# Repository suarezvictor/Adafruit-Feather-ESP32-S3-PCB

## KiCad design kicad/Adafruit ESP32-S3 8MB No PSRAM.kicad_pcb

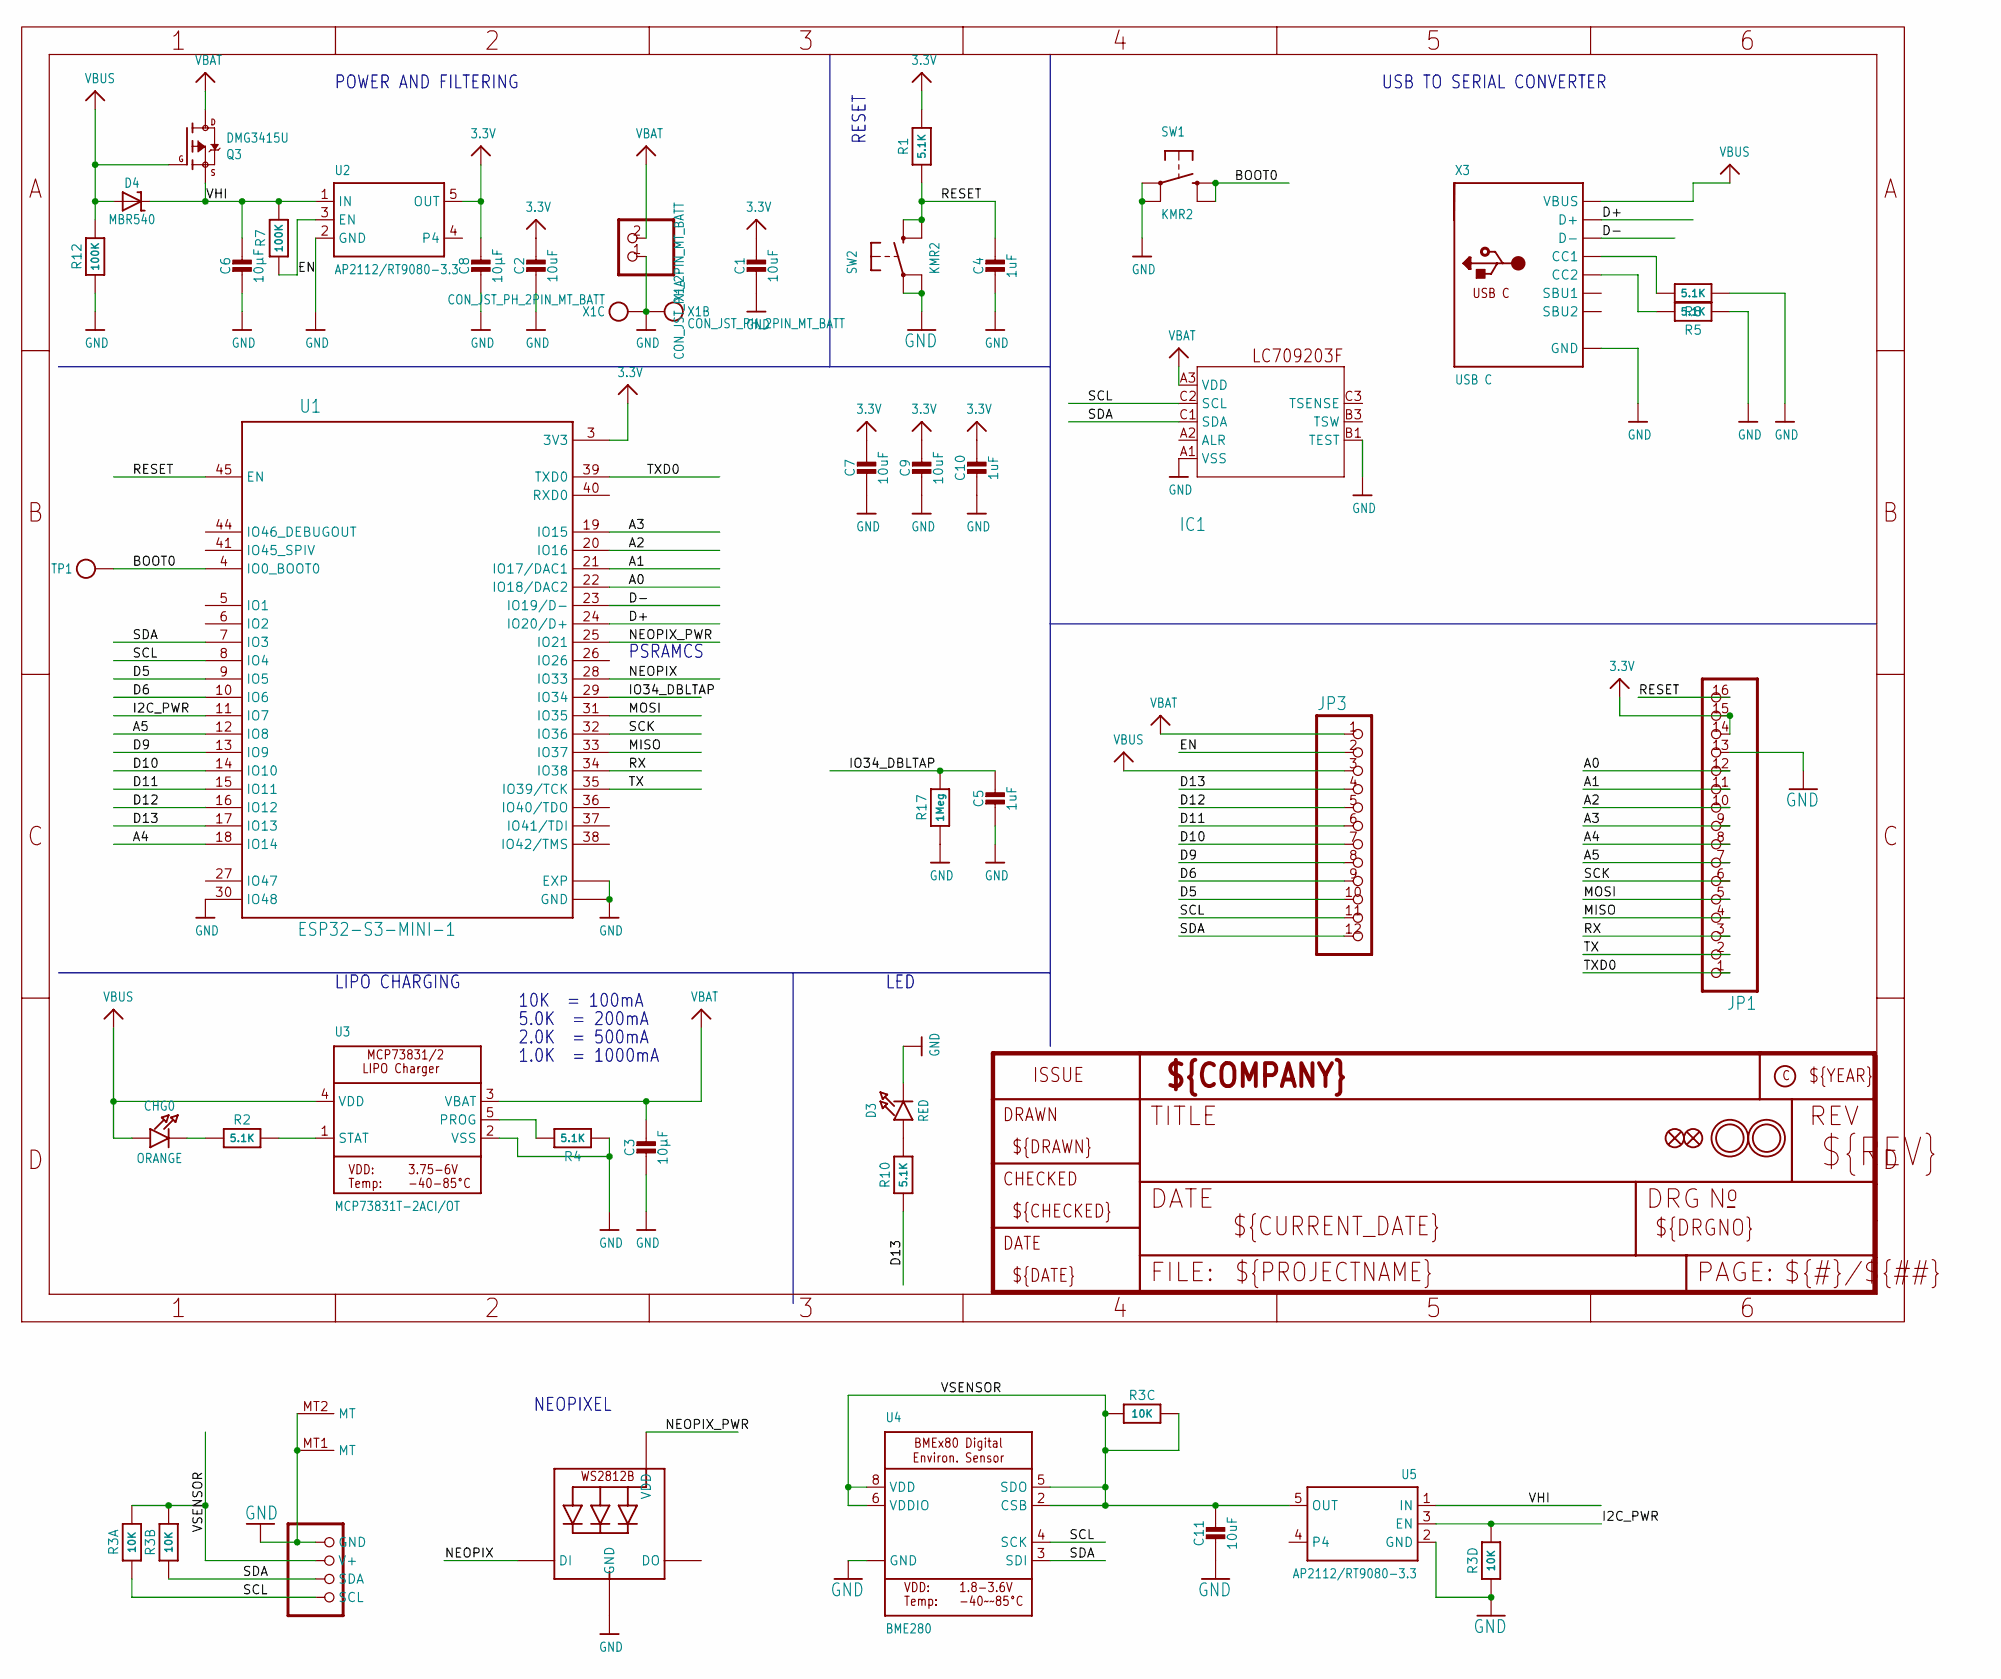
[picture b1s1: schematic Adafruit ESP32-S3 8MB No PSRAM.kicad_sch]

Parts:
C1, C2, C7, C9: 10uF; 0805-NO
C3, C6, C8: 10µF; 0805-NO
C4, C5, C10: 1uF; 0603-NO
C11: 10uF; _0805MP
CHG0: ORANGE; CHIPLED_0603_NOOUTLINE
CONN1: STEMMA_I2C_QTRA; JST_SH4_RA
D3: RED; CHIPLED_0603_NOOUTLINE
D4: MBR540; SOD-123
IC1: LC709203F/MH; WLCSP9
JP1: HEADER-1X16ROUND; 1X16_ROUND
JP3: HEADER-1X12; 1X12_ROUND
LED1: WS2812B_SK6805_1515; SK6805_1515
Q3: DMG3415U; SOT23-R
R1, R2, R4, R5, R8, R10: 5.1K; 0603-NO
R3: 10K; RESPACK_4X0603
R7, R12: 100K; 0603-NO
R17: 1Meg; 0603-NO
SW1, SW2: KMR2; BTN_KMR2_4.6X2.8
TP1: TESTPOINTROUND1.5MMNO; TESTPOINT_ROUND_1.5MM_NO
U1: ESP32-S3-MINI-1; QFN60_ESP32-S2-MINI-1_EXP
U2, U5: AP2112/RT9080-3.3; SOT23-5
U3: MCP73831T-2ACI/OT; SOT23-5
U4: BME280
U$31, U$32: MOUNTINGHOLE2.5; MOUNTINGHOLE_2.5_PLATED
U$34, U$35: FIDUCIAL_1MM
X1: CON_JST_PH_2PIN_MT_BATT; JSTPH2_BATT
X3: USB C; USB_C_CUSB31-CFM2AX-01-X

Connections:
3.3V: C1.1, C2.1, C7.1, C8.1, C9.1, C10.1, JP1.14, JP1.15, R1.2, U1.3 (3V3), U2.5 (OUT)
A0: JP1.12, U1.22 (IO18/DAC2)
A1: JP1.11, U1.21 (IO17/DAC1)
A2: JP1.10, U1.20 (IO16)
A3: JP1.9, U1.19 (IO15)
A4: JP1.8, U1.18 (IO14)
A5: JP1.7, U1.12 (IO8)
BOOT0: SW1.B (S), SW1.B' (S1), TP1.P$1, U1.4 (IO0_BOOT0)
D5: JP3.10, U1.9 (IO5)
D6: JP3.9, U1.10 (IO6)
D9: JP3.8, U1.13 (IO9)
D10: JP3.7, U1.14 (IO10)
D11: JP3.6, U1.15 (IO11)
D12: JP3.5, U1.16 (IO12)
D13: JP3.4, R10.1, U1.17 (IO13)
D+: U1.24 (IO20/D+), X3.A6 (D+), X3.B6 (D+)
D-: U1.23 (IO19/D-), X3.A7 (D-), X3.B7 (D-)
EN: JP3.2, R7.1, U2.3 (EN)
GND: C1.2, C2.2, C3.2, C4.2, C5.2, C6.2, C7.2, C8.2, C9.2, C10.2, C11.2, CONN1.1 (GND), CONN1.MT1 (MT), CONN1.MT2 (MT), D3.C, IC1.A1 (VSS), IC1.B1 (TEST), JP1.13, LED1.4 (GND), R3.4 (1), R4.1, R5.1, R8.1, R12.1, R17.1, SW1.A, SW1.A' (P1), SW2.A, SW2.A' (P1), U1.1 (GND), U1.2 (GND), U1.30 (IO48), U1.42 (GND), U1.43 (GND), U1.46 (GND), U1.47 (GND), U1.48 (GND), U1.49 (GND), U1.50 (GND), U1.51 (GND), U1.52 (GND), U1.53 (GND), U1.54 (GND), U1.55 (GND), U1.56 (GND), U1.57 (GND), U1.58 (GND), U1.59 (GND), U1.60 (GND), U1.61 (EXP), U1.62 (GND), U1.63 (GND), U1.64 (GND), U1.65 (GND), U1.66 (EXP), U1.67 (EXP), U1.68 (EXP), U1.69 (EXP), U1.70 (EXP), U1.71 (EXP), U1.72 (EXP), U1.73 (EXP), U2.2 (GND), U3.2 (VSS), U4.1 (GND), U4.7 (GND), U5.2 (GND), X1.1, X1.NC1, X1.NC2, X3.A1B12 (GND), X3.B1A12 (GND)
I2C_PWR: R3.5 (2), U1.11 (IO7), U5.3 (EN)
IO34_DBLTAP: C5.1, R17.2, U1.29 (IO34)
MISO: JP1.4, U1.33 (IO37)
MOSI: JP1.5, U1.31 (IO35)
unnamed: CHG0.C, R2.1
unnamed: R2.2, U3.1 (STAT)
unnamed: R4.2, U3.5 (PROG)
unnamed: D3.A, R10.2
unnamed: R8.2, X3.A5 (CC1)
unnamed: R5.2, X3.B5 (CC2)
NEOPIX: LED1.1 (DI), U1.28 (IO33)
NEOPIX_PWR: LED1.2 (VDD), U1.25 (IO21)
RESET: C4.1, JP1.16, R1.1, SW2.B (S), SW2.B' (S1), U1.45 (EN)
RX: JP1.3, U1.34 (IO38)
SCK: JP1.6, U1.32 (IO36)
SCL: CONN1.4 (SCL), IC1.C2 (SCL), JP3.11, R3.1, U1.8 (IO4), U4.4 (SCK)
SDA: CONN1.3 (SDA), IC1.C1 (SDA), JP3.12, R3.2 (1), U1.7 (IO3), U4.3 (SDI)
TX: JP1.2, U1.35 (IO39/TCK)
TXD0: JP1.1, U1.39 (TXD0)
VBAT: C3.1, IC1.A3 (VDD), JP3.1, Q3.3 (D), U3.3 (VBAT), X1.2
VBUS: CHG0.A, D4.A, JP3.3, Q3.1 (G), R12.2, U3.4 (VDD), X3.A4B9 (VBUS), X3.B4A9 (VBUS)
VHI: C6.1, D4.C, Q3.2 (S), R7.2, U2.1 (IN), U5.1 (IN)
VSENSOR: C11.1, CONN1.2 (V+), R3.3 (1), R3.6 (2), R3.7 (2), R3.8 (2), U4.2 (CSB), U4.5 (SDO), U4.6 (VDDIO), U4.8 (VDD), U5.5 (OUT)

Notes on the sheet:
2.0K = 500mA
POWER AND FILTERING
5.0K = 200mA
RESET
USB TO SERIAL CONVERTER
LIPO CHARGING
PSRAMCS
1.0K = 1000mA
LED
NEOPIXEL
10K = 100mA

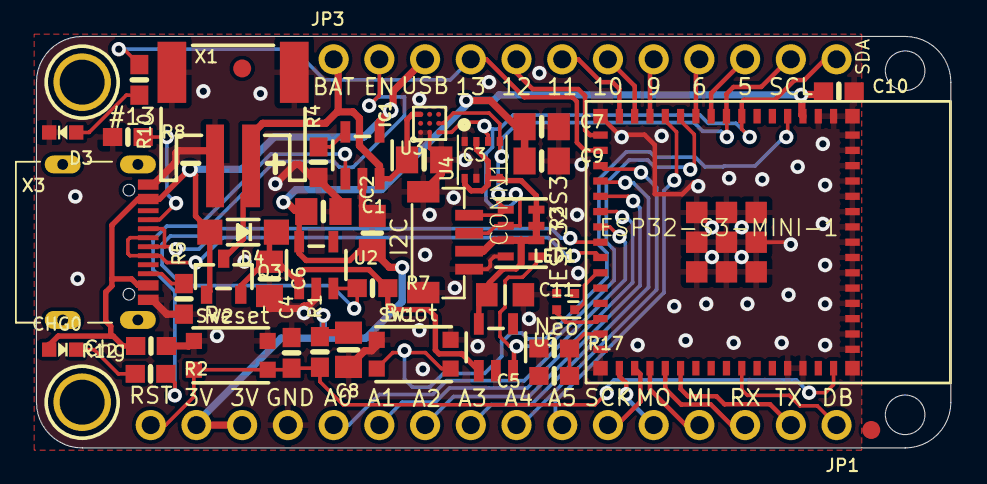
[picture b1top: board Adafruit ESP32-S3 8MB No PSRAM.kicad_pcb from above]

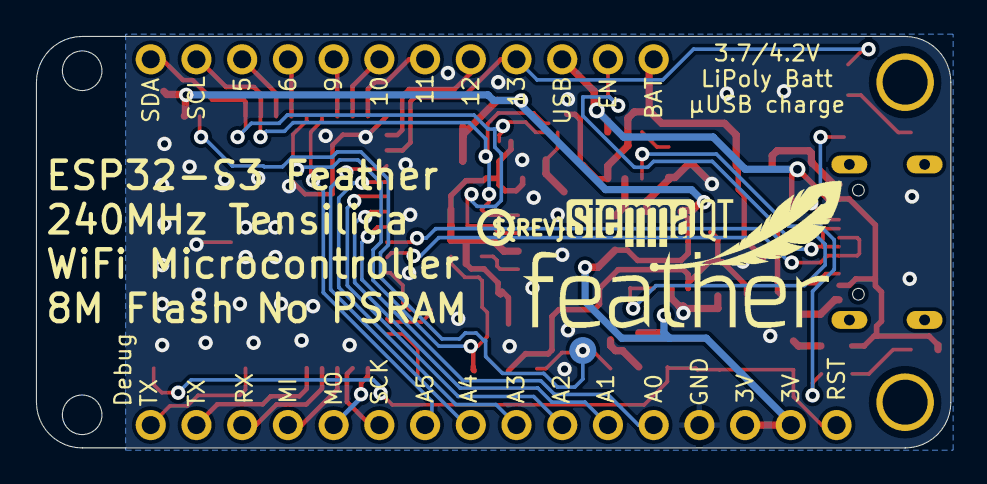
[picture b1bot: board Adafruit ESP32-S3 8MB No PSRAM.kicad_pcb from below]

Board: 2 copper layers, 50.8 x 22.9 mm, 49 parts (4 on the bottom side), 42 nets.

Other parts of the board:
@HOLE0, @HOLE1: (no value)
U$14: PCBFEAT-REV-040
U$15: FEATHERLOGO_MED
U$53: STEMMAQT

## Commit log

2025-09-10 Update Adafruit Feather ESP32-S3 Pinout.pdf
    jst-ph
2025-11-26 conversion to Kicad
